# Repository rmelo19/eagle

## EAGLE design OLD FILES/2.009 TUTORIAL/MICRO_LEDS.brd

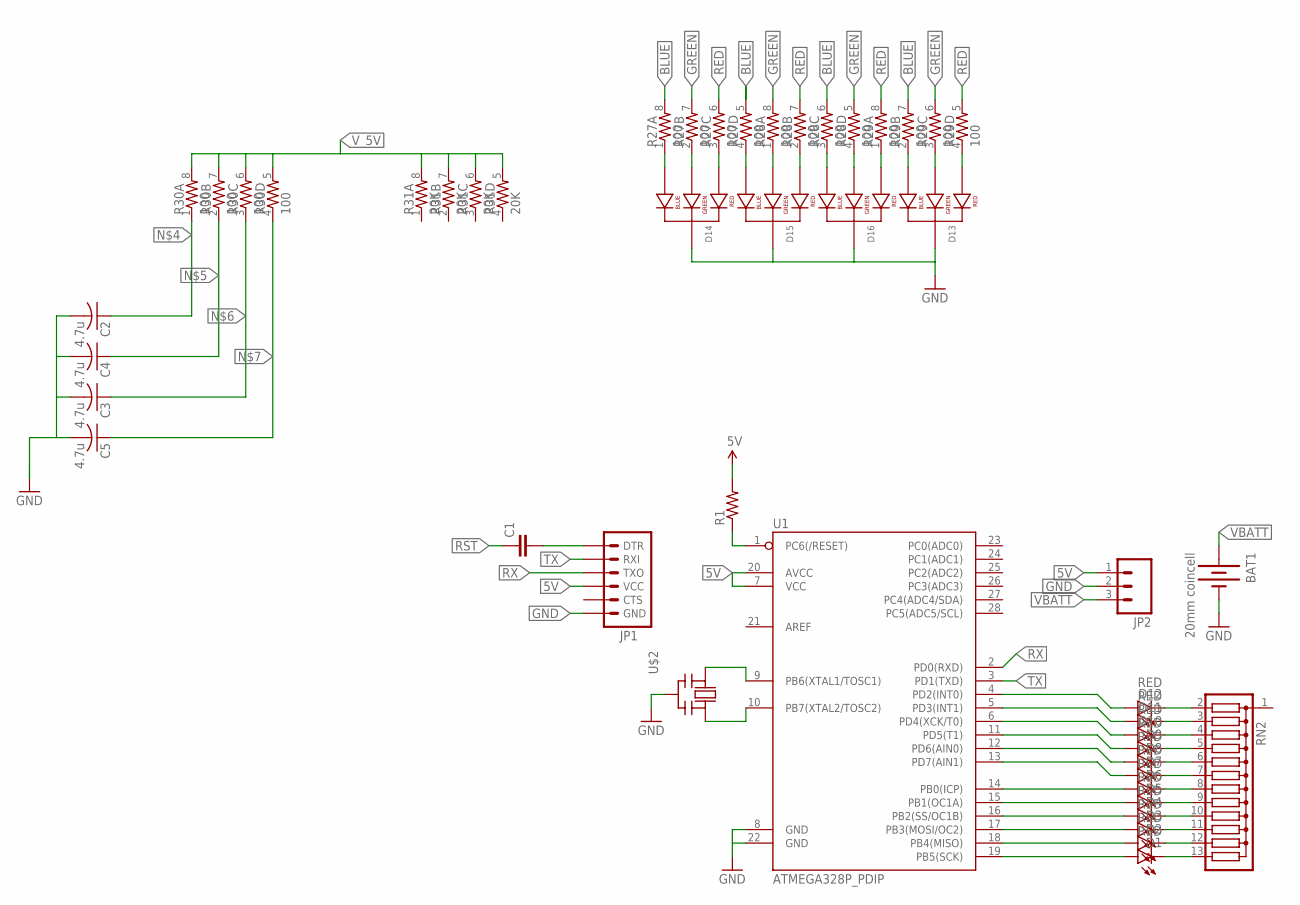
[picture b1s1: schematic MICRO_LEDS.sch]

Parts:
BAT1: 20mm coincell; BATTCOM_20MM_PTH
C1: CAPPTH1; CAP-PTH-5MM
C2, C3, C4, C5: 4.7u; C0805
D1, D2, D3, D4, D5, D6, D7, D8, D9, D10, D11, D12: RED; LED3MM
D13, D14, D15, D16: LED-RGB-CC-THRUDIFFUSE; LED-RGB-THRU
JP1: ARDUINO_SERIAL_PROGRAMLONGPADS; 1X06_LONGPADS
JP2: M03-SCREW-5MM; SCREWTERMINAL-5MM-3
R1: RESISTORPTH-1/4W; AXIAL-0.4
R27, R28, R29, R30: 100; 0603-ARV
R31: 20K; 0603-ARV
RN2: G12R; SIL13
U1: ATMEGA328P_PDIP; DIL28-3
U$2: CERMOSCILL-THM; CERM_OSC

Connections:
5V: JP1.4 (VCC), JP2.1, R1.P$2 (2), U1.7 (VCC), U1.20 (AVCC)
GND: BAT1.2 (-), C2.2, C3.2, C4.2, C5.2, D13.2 (CATHODE), D14.2 (CATHODE), D15.2 (CATHODE), D16.2 (CATHODE), JP1.6 (GND), JP2.2, U1.8 (GND), U1.22 (GND), U$2.P$2 (GND)
unnamed: U1.9 (PB6(XTAL1/TOSC1)), U$2.P$1 (IN)
unnamed: U1.10 (PB7(XTAL2/TOSC2)), U$2.P$3 (OUT)
unnamed: D1.A, U1.19 (PB5(SCK))
unnamed: C2.1, D1.K (C), R30.1, RN2.13
unnamed: C4.1, D2.A, R30.2 (1), U1.18 (PB4(MISO))
unnamed: C3.1, D2.K (C), R30.3 (1), RN2.12
unnamed: C5.1, D3.A, R30.4 (1), U1.17 (PB3(MOSI/OC2))
unnamed: D3.K (C), RN2.11
unnamed: D4.A, U1.16 (PB2(SS/OC1B))
unnamed: D4.K (C), RN2.10
unnamed: D5.A, U1.15 (PB1(OC1A))
unnamed: D5.K (C), RN2.9
unnamed: D6.A, U1.14 (PB0(ICP))
unnamed: D6.K (C), RN2.8
unnamed: D7.A, U1.13 (PD7(AIN1))
unnamed: D8.A, U1.12 (PD6(AIN0))
unnamed: D9.A, U1.11 (PD5(T1))
unnamed: D10.A, U1.6 (PD4(XCK/T0))
unnamed: D11.A, U1.5 (PD3(INT1))
unnamed: D12.A, U1.4 (PD2(INT0))
unnamed: D7.K (C), RN2.7
unnamed: D8.K (C), RN2.6
unnamed: D9.K (C), RN2.5
unnamed: D10.K (C), RN2.4
unnamed: D11.K (C), RN2.3
unnamed: D12.K (C), RN2.2
unnamed: R1.P$1 (1), U1.1 (PC6(/RESET))
unnamed: D14.4 (BLUE_CATHODE), R27.1
unnamed: C1.2, JP1.1 (DTR)
unnamed: D14.3 (GREEN_CATHODE), R27.2 (1)
unnamed: D14.1 (RED_CATHODE), R27.3 (1)
unnamed: D15.4 (BLUE_CATHODE), R27.4 (1)
unnamed: D15.3 (GREEN_CATHODE), R28.1
unnamed: D15.1 (RED_CATHODE), R28.2 (1)
unnamed: D16.4 (BLUE_CATHODE), R28.3 (1)
unnamed: D16.3 (GREEN_CATHODE), R28.4 (1)
unnamed: D16.1 (RED_CATHODE), R29.1
unnamed: D13.4 (BLUE_CATHODE), R29.2 (1)
unnamed: D13.3 (GREEN_CATHODE), R29.3 (1)
unnamed: D13.1 (RED_CATHODE), R29.4 (1)
RST: C1.1
RX: JP1.3 (TXO), U1.2 (PD0(RXD))
TX: JP1.2 (RXI), U1.3 (PD1(TXD))
VBATT: BAT1.1 (+), JP2.3
V_5V: R30.5 (2), R30.6 (2), R30.7 (2), R30.8 (2), R31.5 (2), R31.6 (2), R31.7 (2), R31.8 (2)

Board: 2 copper layers, 33 parts (0 on the bottom side), 46 nets, no tracks yet.

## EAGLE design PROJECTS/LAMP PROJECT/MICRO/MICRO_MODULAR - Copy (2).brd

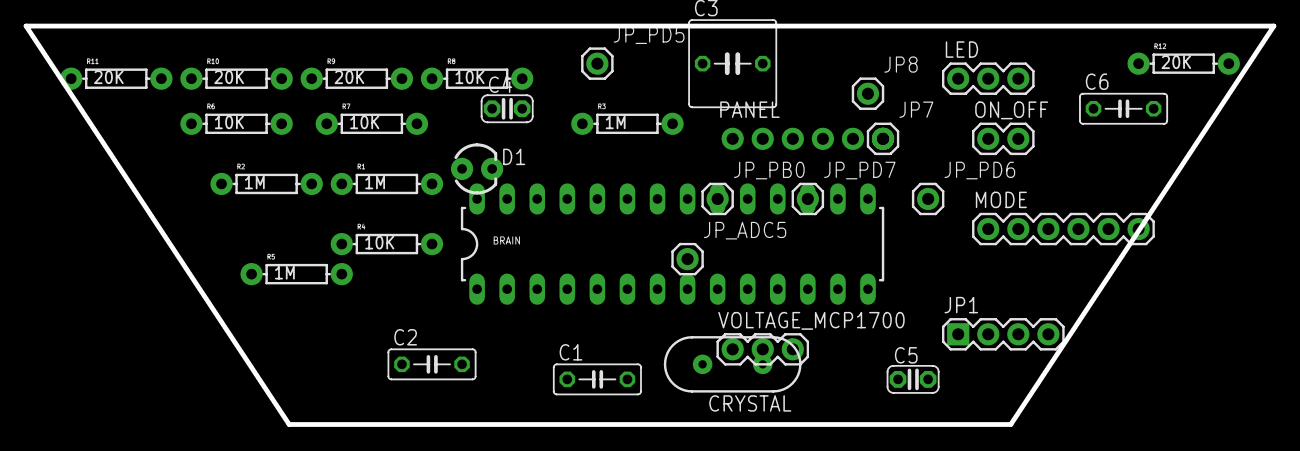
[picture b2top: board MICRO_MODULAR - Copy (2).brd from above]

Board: 2 copper layers, 105.4 x 33.7 mm, 34 parts (0 on the bottom side), 30 nets, no tracks yet.

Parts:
BRAIN: ATMEGA328P_PDIP; DIL-28-3
C1, C2, C6: 1u; C050-025X075
C3: 1000uF; C050-075X075
C4, C5: 22pF; C025-024X044
CRYSTAL: HC49US
D1: LED3MM
JP1: 1X04
JP7, JP8: 1X01
JP_ADC5: 1X01
JP_PB0: 1X01
JP_PD5, JP_PD6, JP_PD7: 1X01
LED: 1X03
MODE: 1X06
ON_OFF: 1X02
PANEL: 1X06_NO_SILK
R1, R2, R3, R5: 1M; AXIAL-0.3
R4, R6, R7, R8: 10K; AXIAL-0.3
R9, R10, R11, R12: 20K; AXIAL-0.3
VOLTAGE_MCP1700: 1X03

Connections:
BLUE_BRAIN: BRAIN.25, PANEL.2
GND: BRAIN.8, BRAIN.22, C1.2, C2.2, C3.2, C4.2, C5.2, C6.2, LED.1, MODE.2, ON_OFF.1, PANEL.5, R7.P$2, R9.P$2, VOLTAGE_MCP1700.3
GREEN_BRAIN: BRAIN.24, PANEL.3
LEDS_BRAIN: BRAIN.2, LED.2
unnamed: BRAIN.3, C6.1, R6.P$2, R7.P$1
unnamed: BRAIN.15, JP1.1, R5.P$2
unnamed: BRAIN.16, JP1.2, R3.P$2
unnamed: BRAIN.17, JP1.3, R2.P$2
unnamed: BRAIN.18, JP1.4, R1.P$2
unnamed: BRAIN.19, R1.P$1, R2.P$1, R3.P$1, R5.P$1
unnamed: BRAIN.9, C4.1, CRYSTAL.2
unnamed: BRAIN.10, C5.1, CRYSTAL.1
unnamed: BRAIN.5, JP8.1
unnamed: D1.K, R8.P$2
unnamed: BRAIN.6, R8.P$1
unnamed: BRAIN.4, JP7.1
unnamed: BRAIN.27, MODE.3, R9.P$1, R10.P$2
unnamed: BRAIN.12, JP_PD6.1
unnamed: BRAIN.13, JP_PD7.1
unnamed: BRAIN.14, JP_PB0.1
unnamed: BRAIN.28, JP_ADC5.1
unnamed: BRAIN.11, JP_PD5.1
unnamed: MODE.6, R12.P$1
unnamed: MODE.5, R11.P$1, R12.P$2
unnamed: MODE.4, R10.P$1, R11.P$2
RED_BRAIN: BRAIN.26, PANEL.1
RST: BRAIN.1, R4.P$1
SPEED_BRAIN: BRAIN.23, PANEL.4
SWITCH_BRAIN: C2.1, C3.1, LED.3, ON_OFF.2, R6.P$1, VOLTAGE_MCP1700.2
V_5V: BRAIN.7, BRAIN.20, C1.1, D1.A, MODE.1, PANEL.6, R4.P$2, VOLTAGE_MCP1700.1

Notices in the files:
parts and their libraries:
SparkFun-Electromechanical: Licensing: Creative Commons ShareAlike 4.0 International - https://creativecommons.org/licenses/by-sa/4.0
